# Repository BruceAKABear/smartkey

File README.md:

# smartkey-hardware

## 智能家居-智能开关

智能开关硬件设计使用kicad进行设计，gerber中已经包含可以直接打板的zip包，如果想去打板，直接将zip包发送至嘉立创打板即可。

智能开关pcb预览图为：

### 硬件设计特性

1. 智能开关硬件尺寸为：L:60mm,W:40mm，可以直接放置在实体开关的暗盒中
2. 提供两路输入控制
3. 对外提供adc和单独一路gpio以及+5V,方便扩展其他硬件

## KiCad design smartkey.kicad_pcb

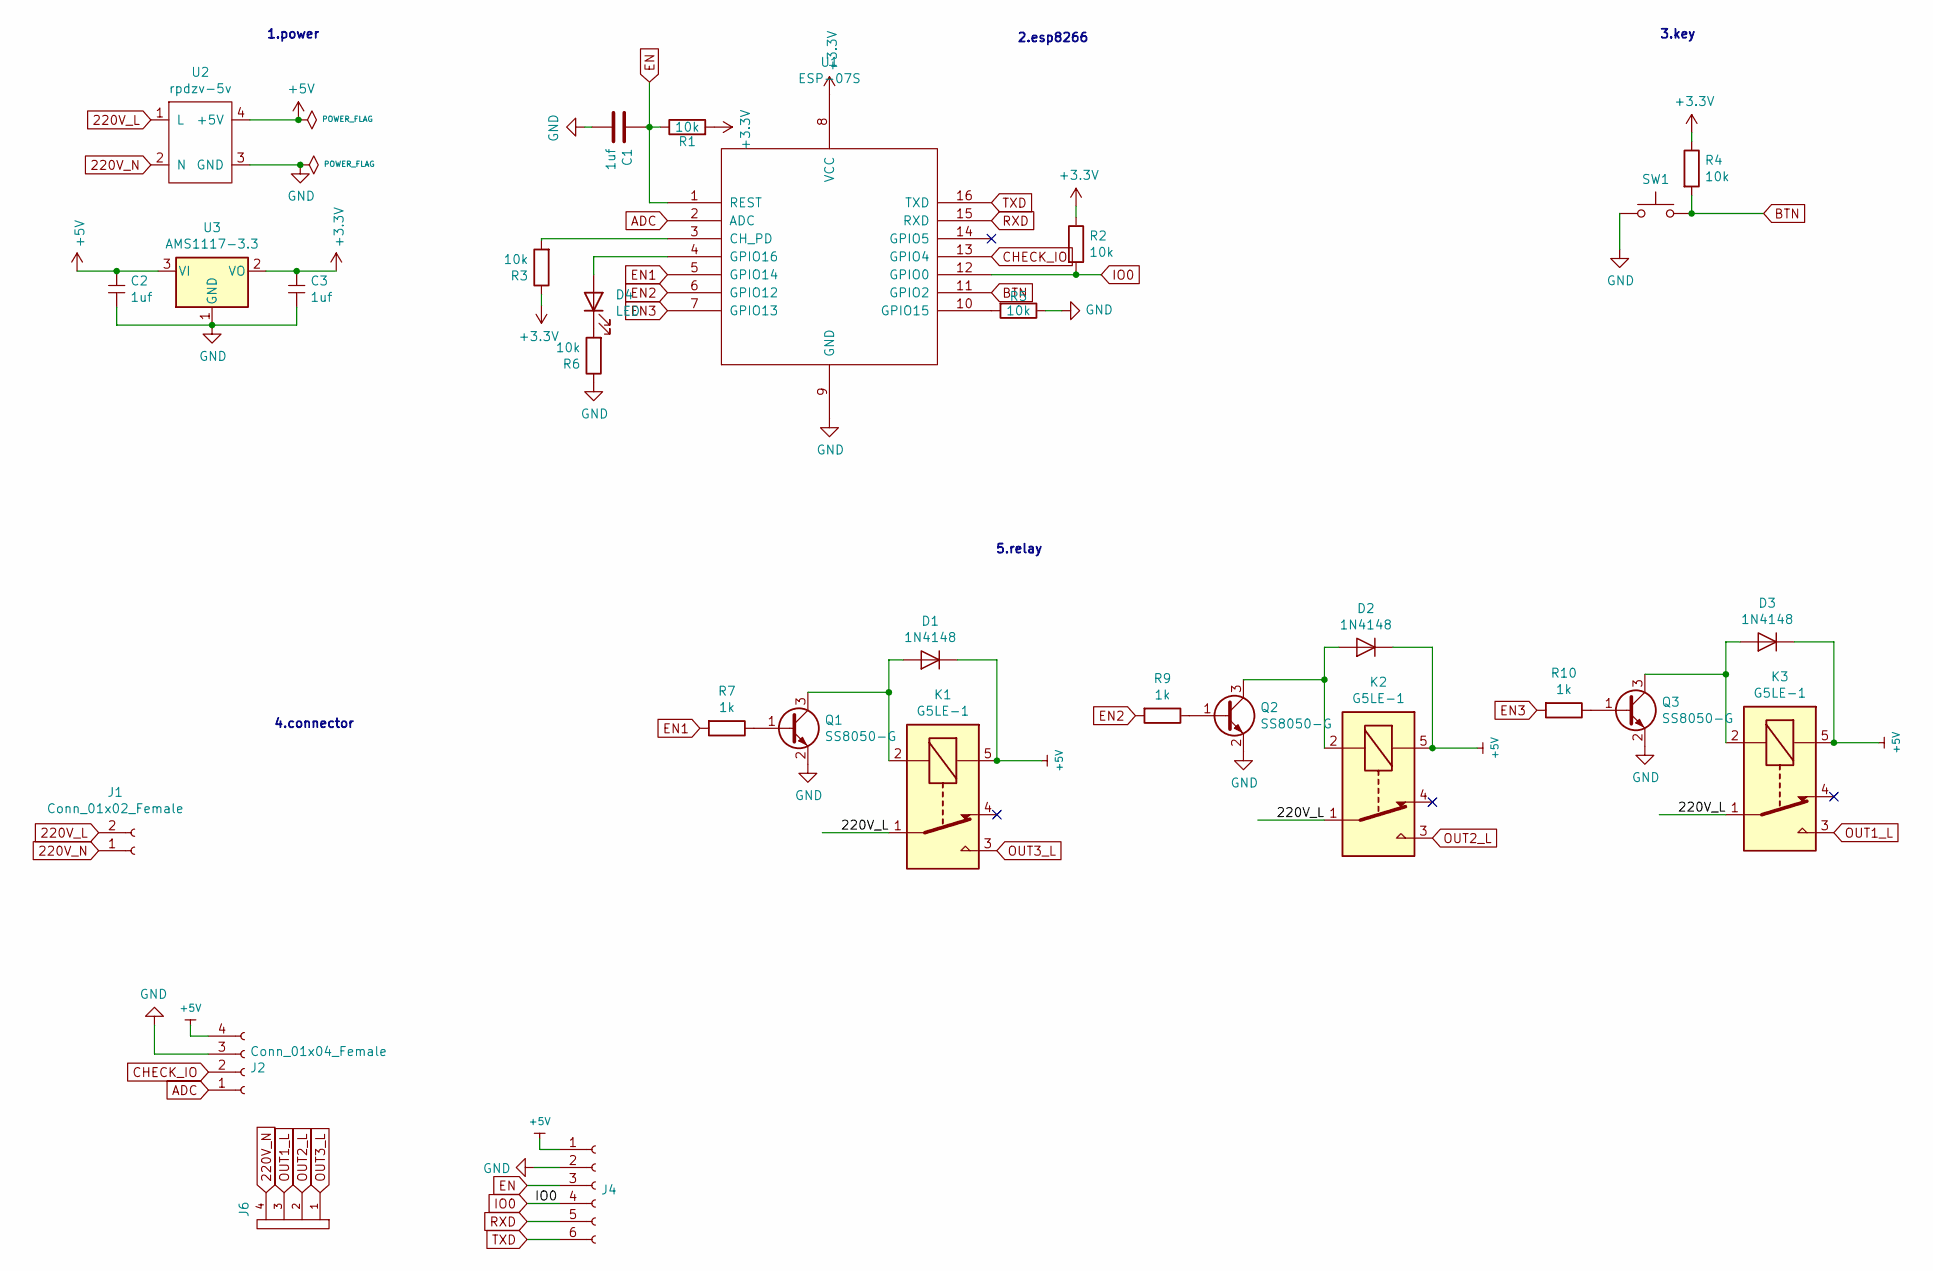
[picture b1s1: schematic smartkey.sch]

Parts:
C1, C2, C3: 1uf; C_0603_1608Metric
D1, D2, D3: 1N4148; D_0603_1608Metric
D4: LED; LED_0603_1608Metric
J1: Conn_01x02_Female; TerminalBlock_bornier-2_P5.08mm
J2: Conn_01x04_Female; TerminalBlock_bornier-4_P5.08mm
J4: Conn_01x06_Female; PinHeader_1x06_P2.00mm_Vertical
J6: CONN-4-conn-4; TerminalBlock_bornier-4_P5.08mm
K1, K2, K3: G5LE-1; Relay_SPDT_Omron-G5LE-1
Q1, Q2, Q3: SS8050-G; SOT-23
R1, R2, R3, R4, R5, R6: 10k; R_0603_1608Metric
R7, R9, R10: 1k; R_0603_1608Metric
SW1: SW_Push; bt-342
U1: ESP-07S
U2: rpdzv-5v; rpdzn-5v
U3: AMS1117-3.3; SOT-223-3_TabPin2

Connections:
220V_L: J1.2, K1.1, K2.1, K3.1, U2.1 (L)
220V_N: J1.1, J6.4, U2.2 (N)
+3V3: C3.1, R1.2, R2.1, R3.1, R4.1, U1.8 (VCC), U3.2 (VO)
ADC: J2.1, U1.2 (ADC)
BTN: R4.2, SW1.2, U1.11 (GPIO2)
CHECK_IO: J2.2, U1.13 (GPIO4)
EN: C1.1, J4.3, R1.1, U1.1 (REST)
EN1: R7.2, U1.5 (GPIO14)
EN2: R9.2, U1.6 (GPIO12)
EN3: R10.2, U1.7 (GPIO13)
IO0: J4.4, R2.2, U1.12 (GPIO0)
unnamed: D1.2 (A), K1.2, Q1.3 (C)
unnamed: D2.2 (A), K2.2, Q2.3 (C)
unnamed: D3.2 (A), K3.2, Q3.3 (C)
unnamed: D4.1 (K), R6.2
unnamed: D4.2 (A), U1.4 (GPIO16)
unnamed: Q1.1 (B), R7.1
unnamed: Q2.1 (B), R9.1
unnamed: Q3.1 (B), R10.1
unnamed: R3.2, U1.3 (CH_PD)
unnamed: R5.2, U1.10 (GPIO15)
OUT1_L: J6.3, K3.3
OUT2_L: J6.2, K2.3
OUT3_L: J6.1, K1.3
RXD: J4.5, U1.15 (RXD)
TXD: J4.6, U1.16 (TXD)

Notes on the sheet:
1.power
2.esp8266
3.key
5.relay
4.connector

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
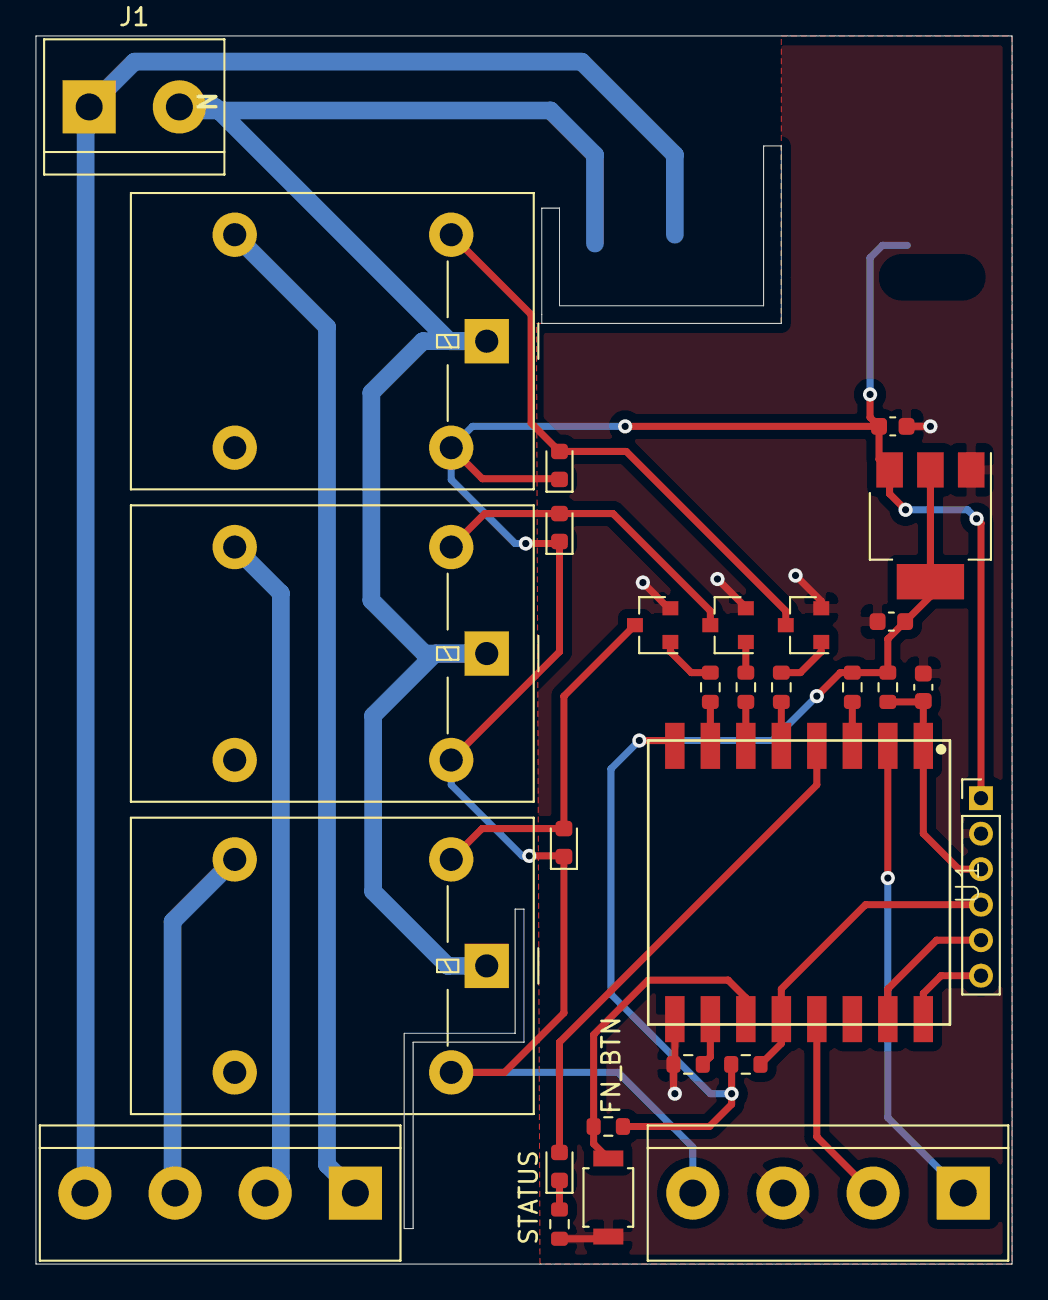
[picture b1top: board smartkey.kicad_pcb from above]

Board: 2 copper layers, 55.0 x 69.2 mm, 30 parts (1 on the bottom side), 28 nets.

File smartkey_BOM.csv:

"Comment","Description","Designator","Footprint","LibRef","Pins","Quantity","PartNumber","url",
"1uf","desc","C3,C2,C1,","C_0603_1608Metric","libref","2","3","","",
"1N4148","desc","D1,D3,D2,","D_0603_1608Metric","libref","2","3","","",
"LED","desc","D4,","LED_0603_1608Metric","libref","2","1","","",
"SS8050-G","desc","Q1,Q3,Q2,","SOT-23","libref","3","3","","",
"10k","desc","R6,R5,R4,R3,R2,R1,","R_0603_1608Metric","libref","2","6","","",
"1k","desc","R7,R10,R9,","R_0603_1608Metric","libref","2","3","","",
"SW_Push","desc","SW1,","bt-342","libref","2","1","","",
"ESP-07S","desc","U1,","ESP-07S","libref","16","1","","",
"AMS1117-3.3","desc","U3,","SOT-223-3_TabPin2","libref","4","1","","",
"Through Hole Items ",
"Conn_01x02_Female","desc","J1,","TerminalBlock_bornier-2_P5.08mm","libref","2","1","","",
"Conn_01x04_Female","desc","J2,","TerminalBlock_bornier-4_P5.08mm","libref","4","1","","",
"Conn_01x06_Female","desc","J4,","PinHeader_1x06_P2.00mm_Vertical","libref","6","1","","",
"CONN-4-conn-4","desc","J6,","TerminalBlock_bornier-4_P5.08mm","libref","4","1","","",
"G5LE-1","desc","K1,K3,K2,","Relay_SPDT_Omron-G5LE-1","libref","5","3","","",
"rpdzv-5v","desc","U2,","rpdzn-5v","libref","7","1","","",

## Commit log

2022-05-08 init
